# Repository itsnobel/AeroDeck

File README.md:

# AeroDeck
A compact, custom-designed handheld wireless and RF auditing tool that is built with the help of the ESP32-C5-WROOM-1 module and sub-1GHz radio modules for cybersecurity project

![Aerodeck PCB design]

And

---

##  Microcontroller Research & Selection
* **Why ESP32-S3 Wasn't Enough:** While popular, the ESP32-S3 fell short of the advanced power efficiency(mainly because I wanted 5GHz wifi support), modern processor architecture, and cutting-edge wireless standards required for a dedicated multi-protocol RF auditing device.
* **Selection of the ESP32-C5-WROOM-1:** After careful research and budgeting for the 65 dollar Hack Club limit, the **ESP32-C5** was chosen as the core microcontroller. It features a modern **RISC-V single-core architecture**, native support for Wi-Fi 6 (802.11ax) and Bluetooth 5, and seamless compatibility with the sub-1GHz CC1101 radio module.

---

## Schematic Design & Hardware Architecture
* **Learning Curve & Software Workflow:** Mastered EasyEDA through video tutorials and multiple initial design hurdles establishing frequent saving habits as i forgot to save the SAME PROJECT 3 TIMESSS!!!, and ensuring absolute precision in schematic capture.
* **Power Management Architecture:** Designed a robust dual-rail power system with USB Type-C port equipped with 5.1k CC resistors for power negotiation, a TP4056 battery charger, a LiPo battery, a slide switch, and a TPS63020 buck-boost regulator to maintain  3.3V rail separated safely from the 5V input.
* **Peripherals & Pin Mapping:**
 I connected all the parts with the help of Ai as i was a beginner. I figured every path and its work by ai and it made me understand and do it by my own. In the process I learnt so many things.
* **Through-Hole Component Adaptation:** Converted standard surface-mount resistors, capacitors, and switches into through-hole packages to ensure effortless hand-soldering. in the next update I will use the main dev board and header pins for more easu soldering.

---

## PCB Layout, Routing, & Manufacturing Prep
* **Component Placement:** Arranged components strategically within a compact 90x65 mm( maybe a little bit bigger as i expanded it later) double-layer board layout, keeping trace lengths as short as possible to minimize signal noise and interference.
* **Routing & Clearance Optimization:** Used auto routing as it was very easy to use. I set the minimum length of width .4mm. After finishing auto routing i fix some unfinished ones manually and then i made the 3v3 rail and GND more eider.
* **Manufacturing Readiness:** Generated and backed up project source files and the final Gerber (.zip) packages.
* 

## Enclosure & 3D CAD Design

For **Week 2**, a custom two-piece protective enclosure was designed in CAD to house all AeroDeck hardware components cleanly and securely and ensure a mobile device without causing wiring trouble. 

### Key Design Features:
* **Two-Piece Shell Architecture:** Designed with a main bottom housing(for keeping the battery) and a top faceplate(mostly visible from the outside) that features corner alignment tabs for secure assembly.
* **Component Cutouts:** Precise openings modeled for the 0.96-inch OLED screen, navigation switches, and external antenna and USB-C ports.
* **Internal Mounting Standoffs:** Built-in internal supports and wall channels to hold the main AeroDeck PCB and 3.7V LiPo battery firmly in place without loose movement.
* **Tolerances & Clearance:** Designed with standard 3D-printing tolerances to ensure all physical modules fit snugly upon printing.
* 

And it would be best to print the whole thing by PLA filament as it has some moving part that will snap the battery in ensuring proper connection with the mainboard.

All source CAD files (`.f3d` and `.3mf`) are available in the `/3D Files` directory.

---

## Repository Structure
* `/pcb` — The EasyEDA schematic and board layout source files(.json).
* `/gerber` — Manufacturing-ready Gerber export packages(.zip).
* `/firmware` — Starter code, pin definitions, and hardware initialization scripts for the ESP32-C5.
* `/3D Files` - The .f3d cad file, .gcode.3mf printable file

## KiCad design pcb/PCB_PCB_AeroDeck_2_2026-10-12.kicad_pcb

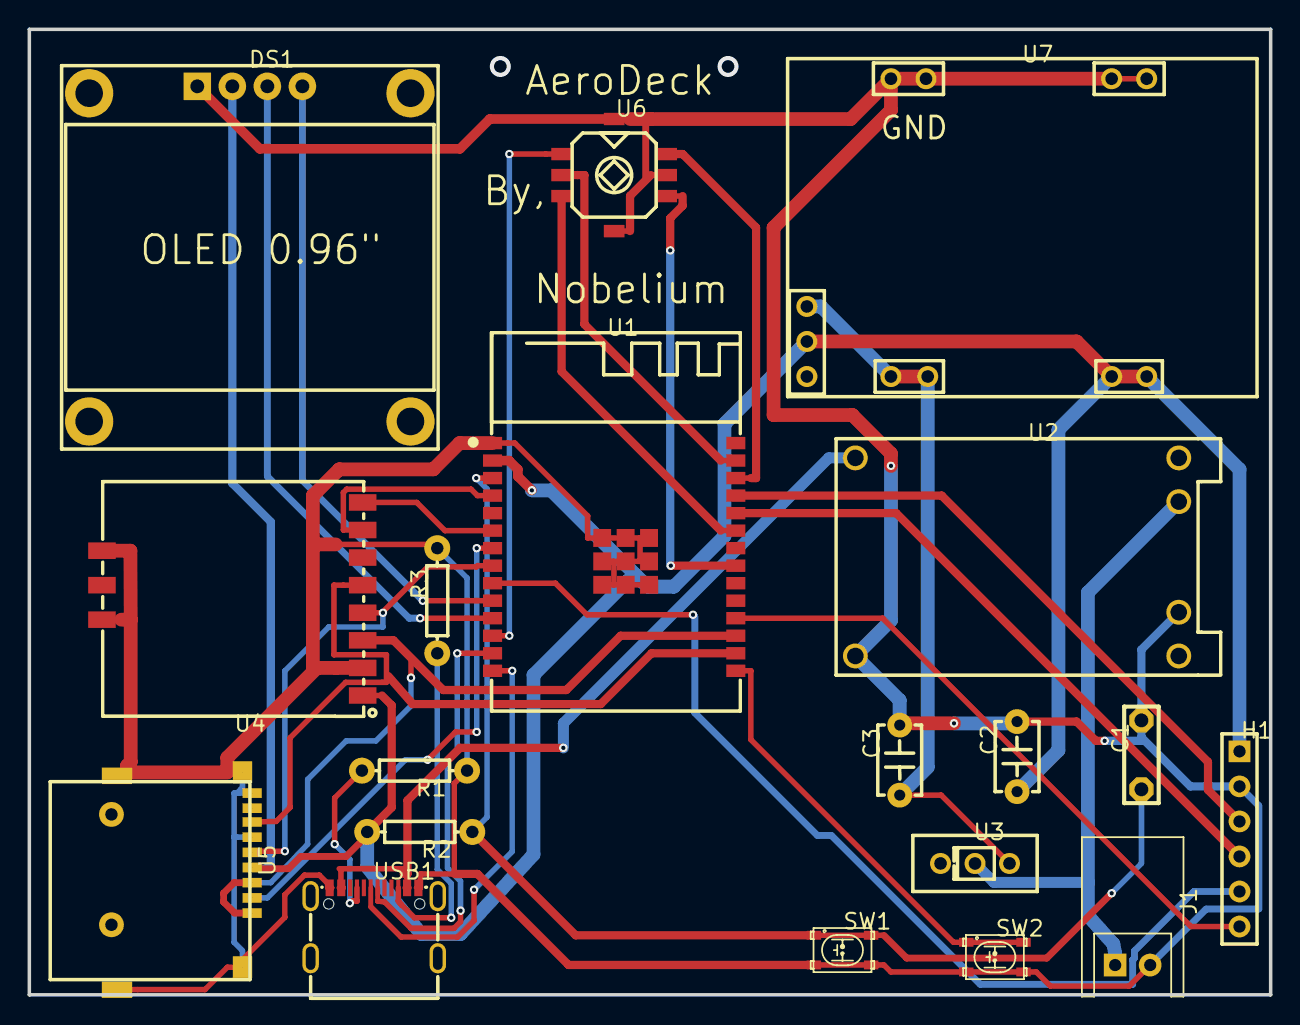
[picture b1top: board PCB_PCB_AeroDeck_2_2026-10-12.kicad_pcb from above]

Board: 2 copper layers, 90.0 x 70.0 mm, 19 parts (0 on the bottom side), 28 nets.

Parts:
C1: 100nF; C-DISC7_21
C2, C3: 10uF; TL_C-DISC-P5.08
DS1: OLED 0.96 INCH 128X64 I2C
H1: HDR-M-1X6
J1: JACK-JST-2P-PW'2.54/90D'; JST-2P-2.54-90D
R1, R3: 5.1kΩ; R_AXIAL-0.3
R2: 10kΩ; R_AXIAL-0.3
SW1, SW2: SKRPACE010; EXIII_SKRPACE010
U1: ESP32-C5-WROOM-1-N16R8-V1.2; COMM-SMD_ESP32-C5-WROOM-1-N16R4
U2: TP4056充电源模块板(TYPE-C); PWRM-TH_TP4056
U3: SS-12D00-G3; SW-TH_3P-L8.8-W3.9-P2.50_SS12D00G3
U4: VT-CC1101-433; WIRELM-SMD_VT-CC1101-433
U5: MICRO SD SOCKET C; MICRO SD SOCKET B
U6: 5-way tactile switch 7mm; 5-WAY TACTILE SWITCH 7MM PCB
U7: TPS63020
USB1: TYPE-C-31-M-26A; USB-C-SMD_TYPE-C-31-M-26A

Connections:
U1_1: C1.2, C2.2, C3.2, DS1.1, H1.2, J1.-, R1.1, R3.2, SW1.3, SW1.4, SW2.3, SW2.4, U1.1, U1.29, U1.30, U1.31, U1.32, U1.33, U1.34, U1.35, U1.36, U1.37, U2.3, U2.6, U4.2, U4.9, U4.11, U5.6, U5.9, U5.10, U5.11, U5.12, U5.13, U6.5, U6.7, U6.8, U7.2, U7.4, USB1.A1, USB1.A12, USB1.B1, USB1.B12
U1_2: C2.1, DS1.2, H1.1, R2.2, U1.2, U4.1, U5.4, U7.3, U7.6
U1_3: C1.1, R2.1, SW1.1, SW1.2, U1.3
U1_4: U1.4, U4.7
U1_6: U1.6, U4.8
U1_7: U1.7, U5.2
U1_8: U1.8, U4.4, U5.5
U1_9: H1.5, U1.9
U1_10: DS1.4, U1.10
U1_11: DS1.3, U1.11
U1_12: U1.12, U6.1
U1_13: U1.13, USB1.A7, USB1.B7
U1_14: U1.14, USB1.A6, USB1.B6
U1_15: SW2.1, SW2.2, U1.15
U1_16: U1.16, U4.5, U5.7
U1_17: U1.17, U4.3, U5.3
U1_18: H1.6, U1.18
U1_21: U1.21, U6.6
U1_23: U1.23, U6.3
U1_24: H1.4, U1.24
U1_25: H1.3, U1.25
U1_26: U1.26, U6.4
U1_27: U1.27, U6.2
U2_2: J1.+, U2.2, U3.2
U3_3: C3.1, U3.3, U7.1, U7.5
USB1_A5: R1.2, USB1.A5
USB1_A9: U2.5, USB1.A4, USB1.A9, USB1.B4, USB1.B9
USB1_B5: R3.1, USB1.B5
